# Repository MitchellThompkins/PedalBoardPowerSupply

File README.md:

## Description
This is a low-cost pedal board power supply for any standard pedal board requiring 9V. It supplies 9V to 8 ports and has a maximum current capacity of 500mA. It takes a standard US 120V 60Hz input and the circuit is protected by a 5x20mm 250VAC 2A fuse. PSpice simulations are also included.

### Current revision of the PCB:

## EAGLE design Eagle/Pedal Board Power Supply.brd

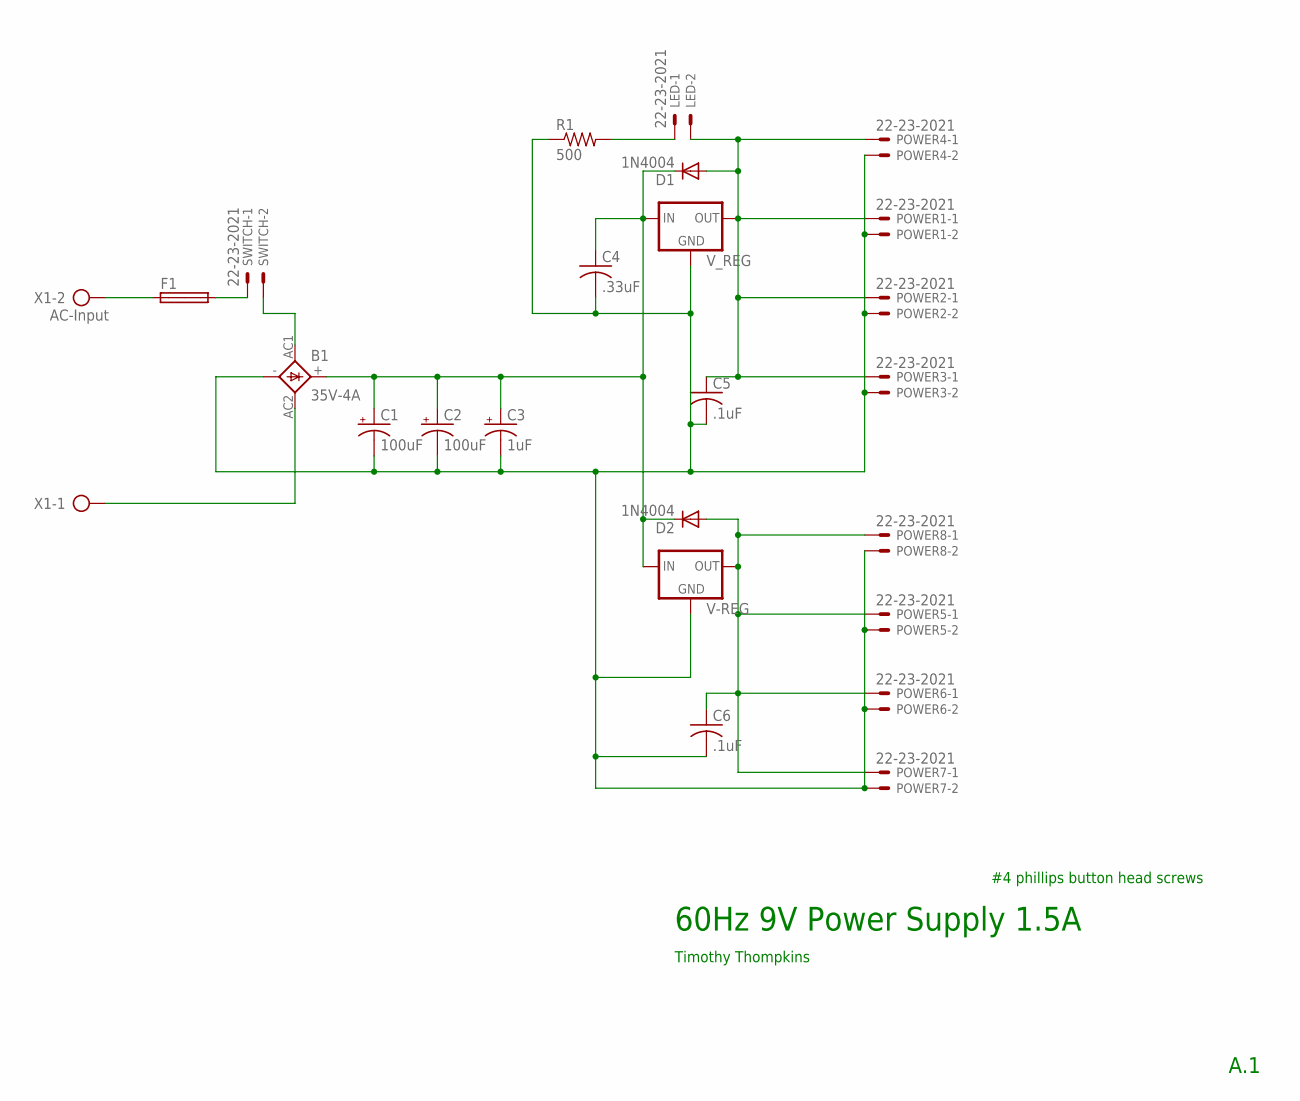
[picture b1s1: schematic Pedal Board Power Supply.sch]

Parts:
B1: 35V-4A; GBL
C1, C2: 100uF; E3,5-10
C3: 1uF; E3,5-10
C4: .33uF; C050-025X075
C5, C6: .1uF; C050-025X075
D1, D2: 1N4004; DO41-10
F1: SHK20Q
LED: 22-23-2021
POWER1, POWER2, POWER3, POWER4, POWER5, POWER6, POWER7, POWER8: 22-23-2021
R1: 500; 0204/7
SWITCH: 22-23-2021
V-REG: V_REG_78XXSINK; TO220-IGO
V_REG: V_REG_78XXSINK; TO220-IGO
X1: AC-Input; AK500/2

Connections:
$N5: B1.AC2, X1.1
GND: B1.-, C1.-, C2.-, C3.-, C4.2, C5.2, C6.2, POWER1.2, POWER2.2, POWER3.2, POWER4.2, POWER5.2, POWER6.2, POWER7.2, POWER8.2, R1.1, V-REG.GND, V_REG.GND
unnamed: F1.1A, X1.2
unnamed: F1.2A, SWITCH.1
unnamed: C5.1, D1.A, LED.2, POWER1.1, POWER2.1, POWER3.1, POWER4.1, V_REG.OUT
unnamed: C6.1, D2.A, POWER5.1, POWER6.1, POWER7.1, POWER8.1, V-REG.OUT
unnamed: LED.1, R1.2
unnamed: B1.AC1, SWITCH.2
V+: B1.+, C1.+, C2.+, C3.+, C4.1, D1.C, D2.C, V-REG.IN, V_REG.IN

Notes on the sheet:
#4 phillips button head screws
60Hz 9V Power Supply 1.5A
A.1
Timothy Thompkins

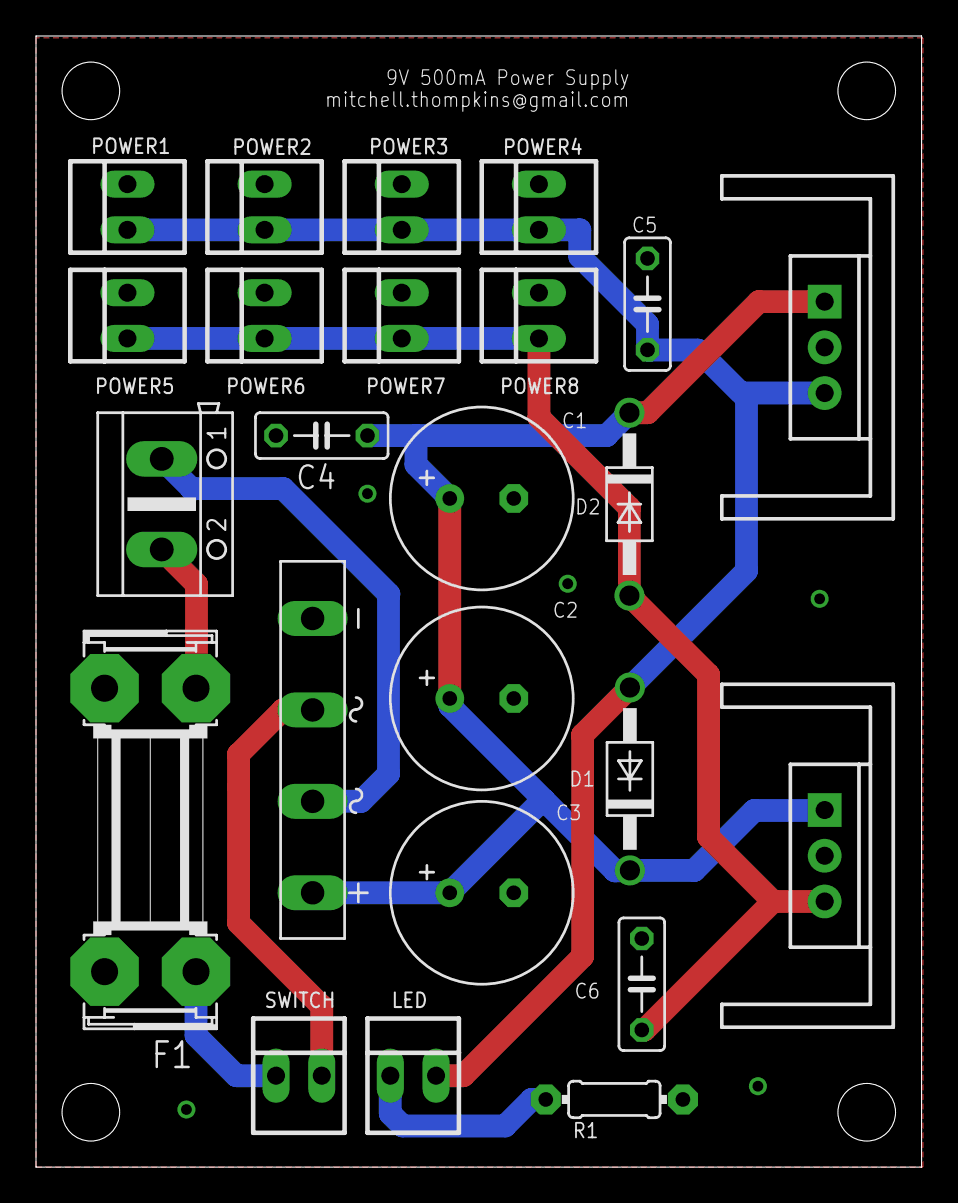
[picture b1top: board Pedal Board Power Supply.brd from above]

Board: 2 copper layers, 49.2 x 62.8 mm, 24 parts (0 on the bottom side), 9 nets.

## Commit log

2016-04-07 Modified Readme

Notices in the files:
parts and their libraries:
SparkFun: Licensing: CC v3.0 Share-Alike You are welcome to use this library for commercial purposes.
